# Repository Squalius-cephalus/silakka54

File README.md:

# Silakka54

Silakka54 is a RP2040 Zero based 54-key column staggered split keyboard. PCB uses hotswap sockets. Design is inpired from REVIUNG41 and Corne keyboards.

PCB is designed for MX style key switches. Current top plate only supports MX style switches. 5-pin switches is supported. I recommend using Vial firmware.

[QMK](https://github.com/qmk/qmk_firmwarehttp:// "QMK") and [Vial](https://github.com/vial-kb/vial-qmk "Vial") firmwares has very barebones key mapping. Good for quick testing.

You can find build guide [here.](https://github.com/Squalius-cephalus/silakka54/blob/main/buildguide/README.md "here.")

PCB design uses footprints from [ScottoKeebs](https://github.com/joe-scotto/scottokeebs/tree/main/Extras/ScottoKicad "ScottoKeebs") and [kbd library.](https://github.com/foostan/kbd "kbd library.")

### TODO
1. Clean up code
2. Add RGB support
3. Make default QMK keymap usable

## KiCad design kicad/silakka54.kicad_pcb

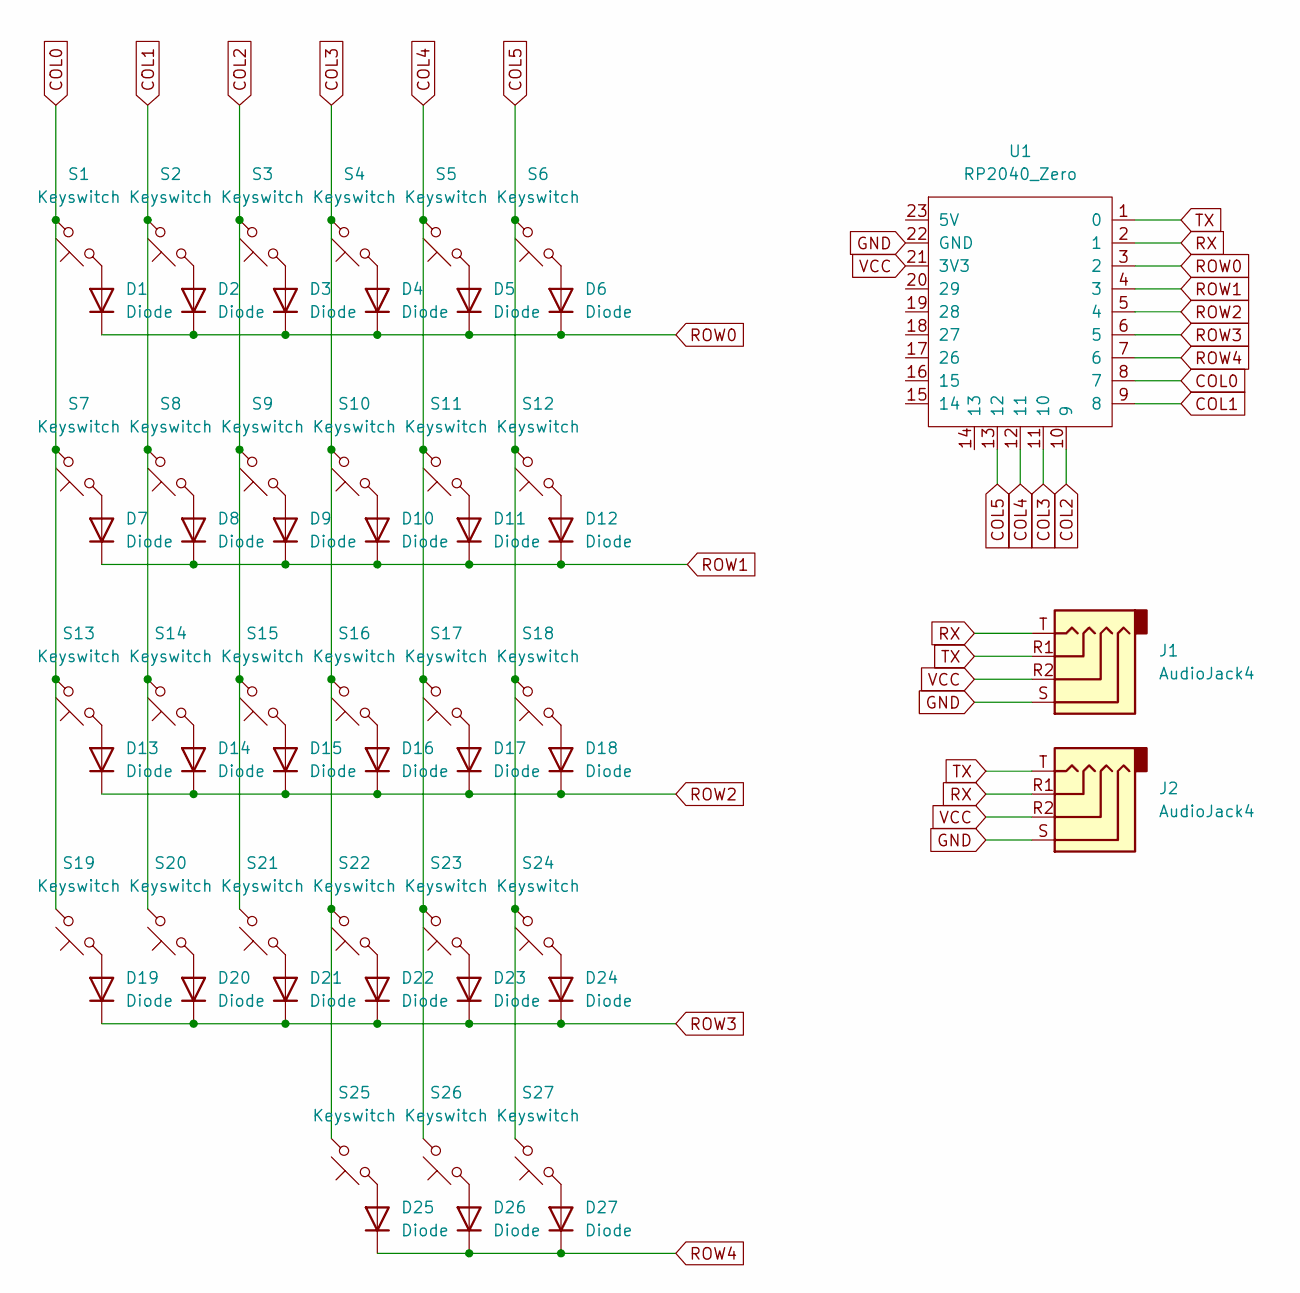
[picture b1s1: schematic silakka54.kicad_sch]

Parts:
D1, D2, D3, D4, D5, D6, D7, D8, D9, D10, D11, D12, D13, D14, D15, D16, D17, D18, D19, D20, D21, D22, D23, D24, D25, D26, D27: Diode; Diode_DO-35
J1, J2: AudioJack4; Jack_3.5mm_PJ320D_Horizontal
S1, S2, S3, S4, S5, S6, S7, S8, S9, S10, S11, S12, S13, S14, S15, S16, S17, S18, S19, S20, S21, S22, S23, S24, S25, S26, S27: Keyswitch; CherryMX_MidHeight_Hotswap
U1: RP2040_Zero

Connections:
COL0: S1.2, S7.2, S13.2, S19.2, U1.8 (7)
COL1: S2.2, S8.2, S14.2, S20.2, U1.9 (8)
COL2: S3.2, S9.2, S15.2, S21.2, U1.10 (9)
COL3: S4.2, S10.2, S16.2, S22.2, S25.2, U1.11 (10)
COL4: S5.2, S11.2, S17.2, S23.2, S26.2, U1.12 (11)
COL5: S6.2, S12.2, S18.2, S24.2, S27.2, U1.13 (12)
GND: J1.S, J2.S, U1.22 (GND)
unnamed: D1.2 (A), S1.1
unnamed: D2.2 (A), S2.1
unnamed: D3.2 (A), S3.1
unnamed: D4.2 (A), S4.1
unnamed: D5.2 (A), S5.1
unnamed: D6.2 (A), S6.1
unnamed: D7.2 (A), S7.1
unnamed: D8.2 (A), S8.1
unnamed: D9.2 (A), S9.1
unnamed: D10.2 (A), S10.1
unnamed: D11.2 (A), S11.1
unnamed: D12.2 (A), S12.1
unnamed: D13.2 (A), S13.1
unnamed: D14.2 (A), S14.1
unnamed: D15.2 (A), S15.1
unnamed: D16.2 (A), S16.1
unnamed: D17.2 (A), S17.1
unnamed: D18.2 (A), S18.1
unnamed: D19.2 (A), S19.1
unnamed: D20.2 (A), S20.1
unnamed: D21.2 (A), S21.1
unnamed: D22.2 (A), S22.1
unnamed: D23.2 (A), S23.1
unnamed: D24.2 (A), S24.1
unnamed: D25.2 (A), S25.1
unnamed: D26.2 (A), S26.1
unnamed: D27.2 (A), S27.1
ROW0: D1.1 (K), D2.1 (K), D3.1 (K), D4.1 (K), D5.1 (K), D6.1 (K), U1.3 (2)
ROW1: D7.1 (K), D8.1 (K), D9.1 (K), D10.1 (K), D11.1 (K), D12.1 (K), U1.4 (3)
ROW2: D13.1 (K), D14.1 (K), D15.1 (K), D16.1 (K), D17.1 (K), D18.1 (K), U1.5 (4)
ROW3: D19.1 (K), D20.1 (K), D21.1 (K), D22.1 (K), D23.1 (K), D24.1 (K), U1.6 (5)
ROW4: D25.1 (K), D26.1 (K), D27.1 (K), U1.7 (6)
RX: J1.T, J2.R1, U1.2 (1)
TX: J1.R1, J2.T, U1.1 (0)
VCC: J1.R2, J2.R2, U1.21 (3V3)

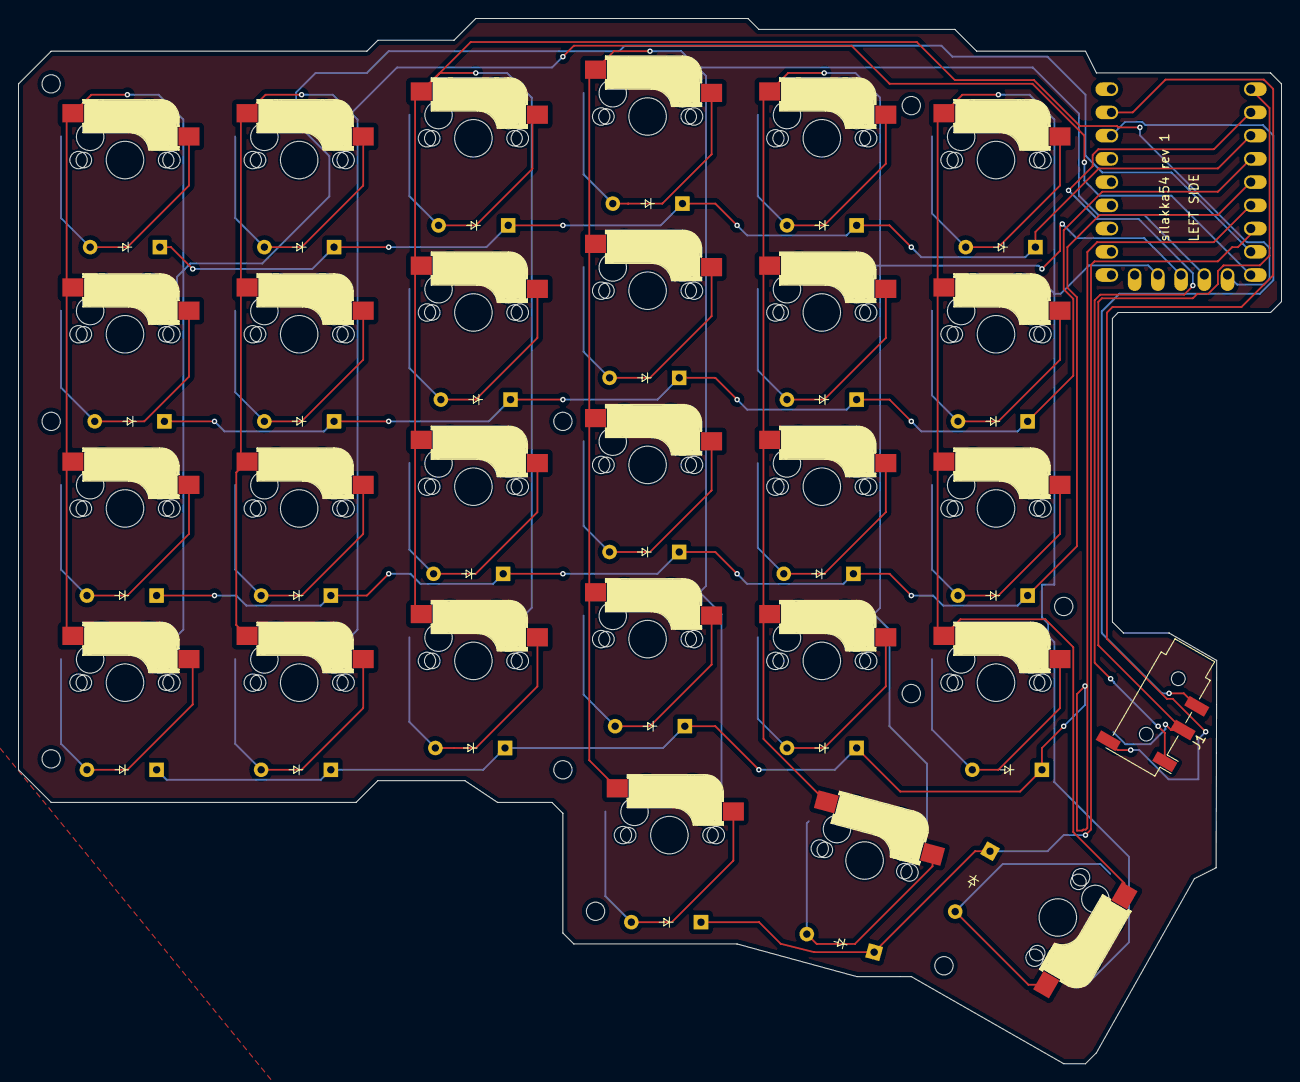
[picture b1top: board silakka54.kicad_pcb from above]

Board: 2 copper layers, 138.1 x 114.2 mm, 57 parts (1 on the bottom side), 42 nets.

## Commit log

2024-09-10 initial commit
    Needs images and code cleaning
2024-09-10 Added images, fixed typos.
2024-09-10 Fixed urls
